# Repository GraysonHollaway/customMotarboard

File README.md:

# Custom Motarboard
Gerber and KiCad files used to make a custom mortarboard decoration for graduation.
This custom PCB sits on top of your gaduation cap and spells out 'ECE OSU' in amber LEDs using a custom designed state machine. 
The clock was implemented with a monostable 555 timer producing an approxamate square wave with tau on the order of 100 milliseconds 
The LEDs are contolled with an NPN BJT such that the digital and analog sections of the circuit are seperated.

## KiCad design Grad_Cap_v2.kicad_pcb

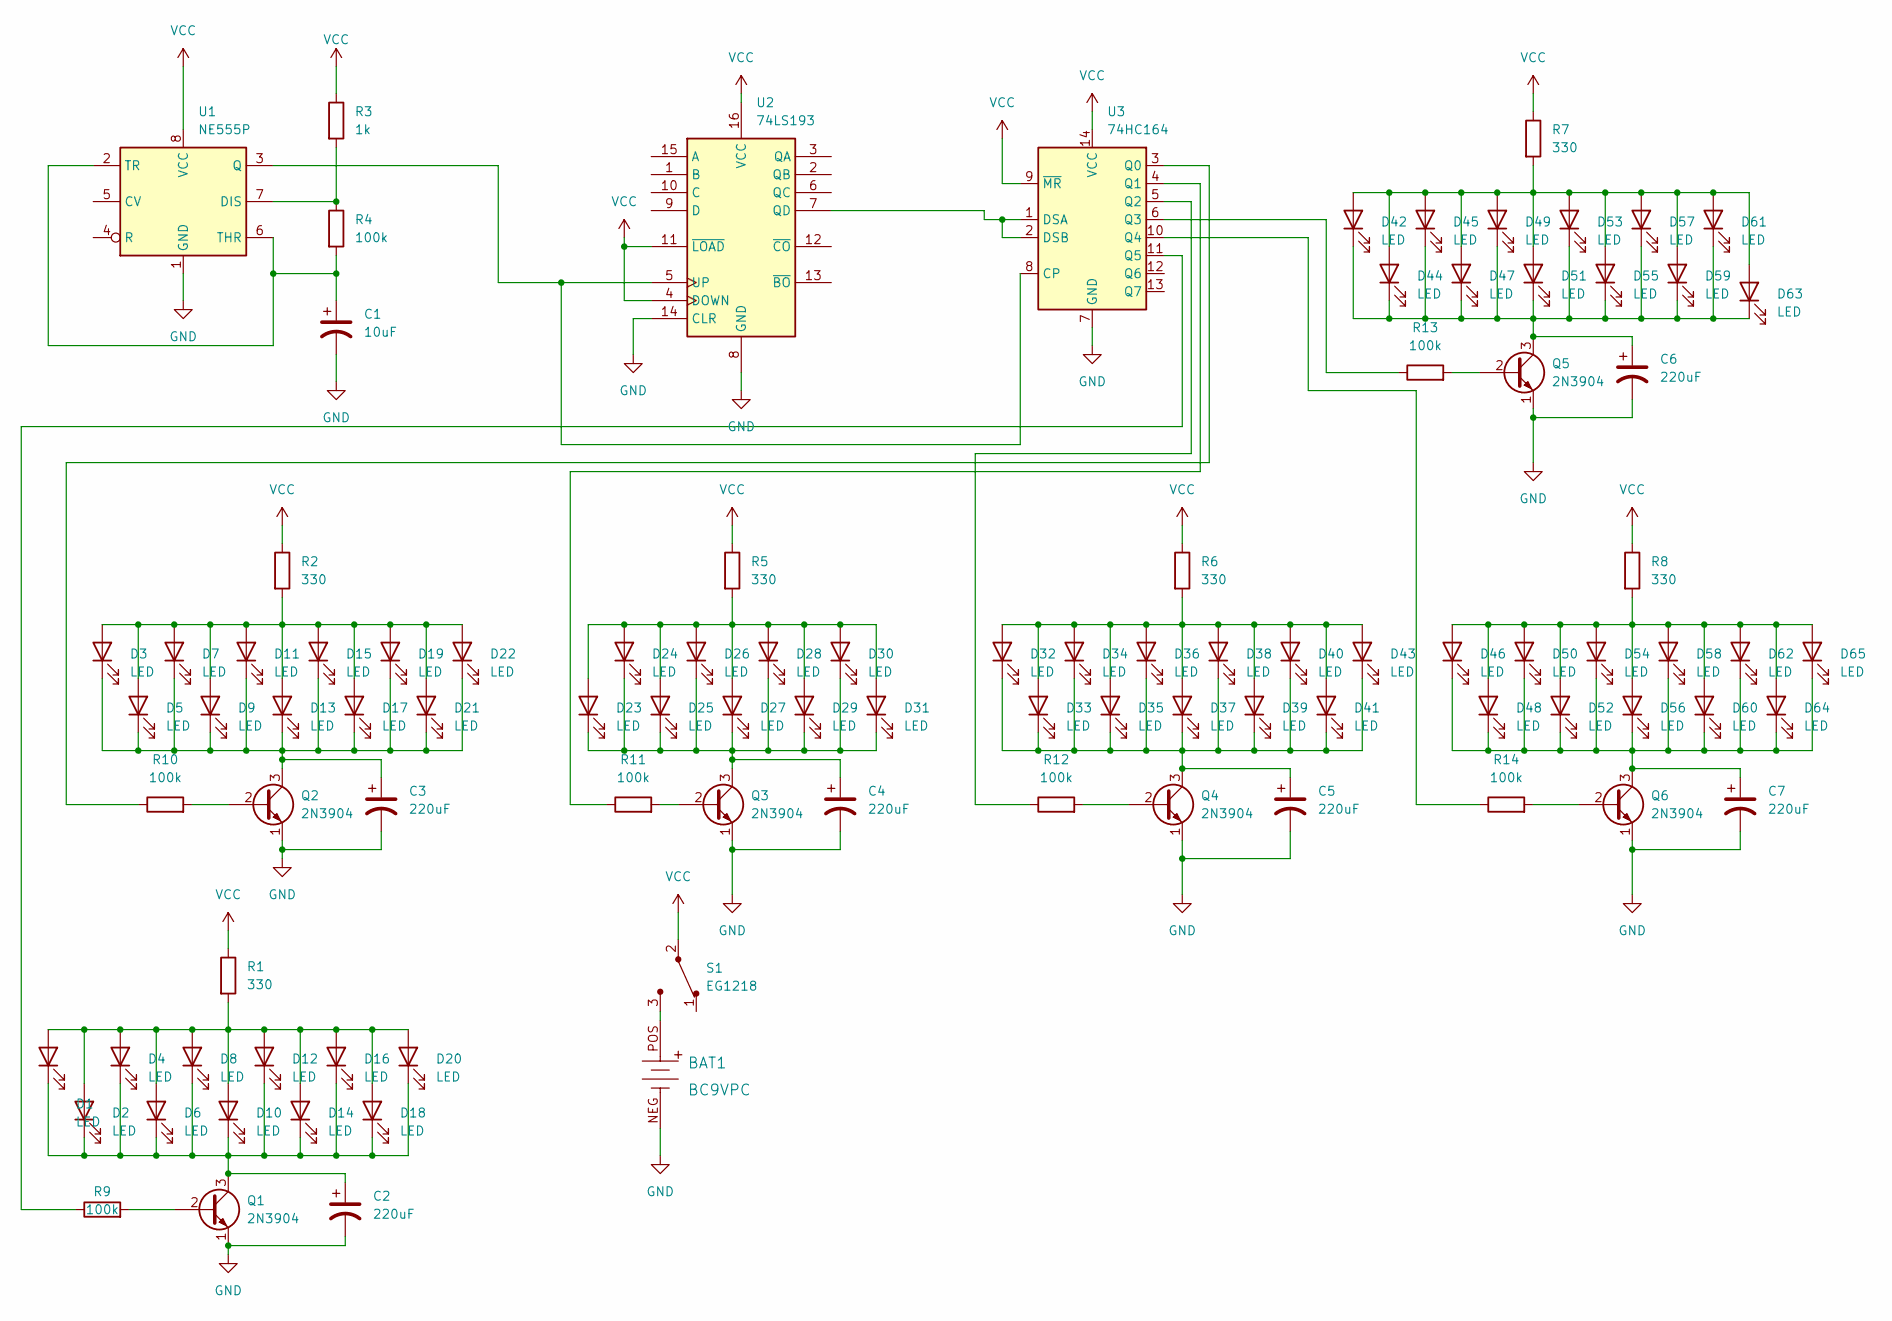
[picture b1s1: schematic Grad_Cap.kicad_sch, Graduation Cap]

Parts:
BAT1: BC9VPC; Battery_Holder_9V_BC9VPC-ND; MPN BC9VPC; Digi-Key_PN BC9VPC-ND
C1: 10uF; CP_Radial_D4.0mm_P2.00mm
C2, C3, C4, C5, C6, C7: 220uF; CP_Radial_D4.0mm_P2.00mm
D1, D2, D3, D4, D5, D6, D7, D8, D9, D10, D11, D12, D13, D14, D15, D16, D17, D18, D19, D20, D21, D22, D23, D24, D25, D26, D27, D28, D29, D30, D31, D32, D33, D34, D35, D36, D37, D38, D39, D40, D41, D42, D43, D44, D45, D46, D47, D48, D49, D50, D51, D52, D53, D54, D55, D56, D57, D58, D59, D60, D61, D62, D63, D64, D65: LED; LED_D5.0mm
Q1, Q2, Q3, Q4, Q5, Q6: 2N3904; TO-92_Inline
R1, R2, R5, R6, R7, R8: 330; R_Axial_DIN0309_L9.0mm_D3.2mm_P12.70mm_Horizontal
R3: 1k; R_Axial_DIN0309_L9.0mm_D3.2mm_P12.70mm_Horizontal
R4, R9, R10, R11, R12, R13, R14: 100k; R_Axial_DIN0309_L9.0mm_D3.2mm_P12.70mm_Horizontal
S1: EG1218; Switch_Slide_11.6x4mm_EG1218; MPN EG1218; Digi-Key_PN EG1903-ND
U1: NE555P; DIP-8_W7.62mm
U2: 74LS193; DIP-16_W7.62mm_Socket
U3: 74HC164; DIP-14_W7.62mm

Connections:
GND: BAT1.NEG, C1.2, C2.2, C3.2, C4.2, C5.2, C6.2, C7.2, Q1.1 (E), Q2.1 (E), Q3.1 (E), Q4.1 (E), Q5.1 (E), Q6.1 (E), U1.1 (GND), U2.8 (GND), U2.14 (CLR), U3.7 (GND)
unnamed: BAT1.POS, S1.3
unnamed: C1.1, R4.2, U1.2 (TR), U1.6 (THR)
unnamed: C2.1, D1.1 (K), D2.1 (K), D4.1 (K), D6.1 (K), D8.1 (K), D10.1 (K), D12.1 (K), D14.1 (K), D16.1 (K), D18.1 (K), D20.1 (K), Q1.3 (C)
unnamed: C3.1, D3.1 (K), D5.1 (K), D7.1 (K), D9.1 (K), D11.1 (K), D13.1 (K), D15.1 (K), D17.1 (K), D19.1 (K), D21.1 (K), D22.1 (K), Q2.3 (C)
unnamed: C4.1, D23.1 (K), D24.1 (K), D25.1 (K), D26.1 (K), D27.1 (K), D28.1 (K), D29.1 (K), D30.1 (K), D31.1 (K), Q3.3 (C)
unnamed: C5.1, D32.1 (K), D33.1 (K), D34.1 (K), D35.1 (K), D36.1 (K), D37.1 (K), D38.1 (K), D39.1 (K), D40.1 (K), D41.1 (K), D43.1 (K), Q4.3 (C)
unnamed: C6.1, D42.1 (K), D44.1 (K), D45.1 (K), D47.1 (K), D49.1 (K), D51.1 (K), D53.1 (K), D55.1 (K), D57.1 (K), D59.1 (K), D61.1 (K), D63.1 (K), Q5.3 (C)
unnamed: C7.1, D46.1 (K), D48.1 (K), D50.1 (K), D52.1 (K), D54.1 (K), D56.1 (K), D58.1 (K), D60.1 (K), D62.1 (K), D64.1 (K), D65.1 (K), Q6.3 (C)
unnamed: D1.2 (A), D2.2 (A), D4.2 (A), D6.2 (A), D8.2 (A), D10.2 (A), D12.2 (A), D14.2 (A), D16.2 (A), D18.2 (A), D20.2 (A), R1.2
unnamed: D3.2 (A), D5.2 (A), D7.2 (A), D9.2 (A), D11.2 (A), D13.2 (A), D15.2 (A), D17.2 (A), D19.2 (A), D21.2 (A), D22.2 (A), R2.2
unnamed: D23.2 (A), D24.2 (A), D25.2 (A), D26.2 (A), D27.2 (A), D28.2 (A), D29.2 (A), D30.2 (A), D31.2 (A), R5.2
unnamed: D32.2 (A), D33.2 (A), D34.2 (A), D35.2 (A), D36.2 (A), D37.2 (A), D38.2 (A), D39.2 (A), D40.2 (A), D41.2 (A), D43.2 (A), R6.2
unnamed: D42.2 (A), D44.2 (A), D45.2 (A), D47.2 (A), D49.2 (A), D51.2 (A), D53.2 (A), D55.2 (A), D57.2 (A), D59.2 (A), D61.2 (A), D63.2 (A), R7.2
unnamed: D46.2 (A), D48.2 (A), D50.2 (A), D52.2 (A), D54.2 (A), D56.2 (A), D58.2 (A), D60.2 (A), D62.2 (A), D64.2 (A), D65.2 (A), R8.2
unnamed: Q1.2 (B), R9.2
unnamed: Q2.2 (B), R10.2
unnamed: Q3.2 (B), R11.2
unnamed: Q4.2 (B), R12.2
unnamed: Q5.2 (B), R13.2
unnamed: Q6.2 (B), R14.2
unnamed: R3.2, R4.1, U1.7 (DIS)
unnamed: R9.1, U3.11 (Q5)
unnamed: R10.1, U3.3 (Q0)
unnamed: R11.1, U3.4 (Q1)
unnamed: R12.1, U3.5 (Q2)
unnamed: R13.1, U3.6 (Q3)
unnamed: R14.1, U3.10 (Q4)
unnamed: U1.3 (Q), U2.5 (UP), U3.8 (CP)
unnamed: U2.7 (QD), U3.1 (DSA), U3.2 (DSB)
VCC: R1.1, R2.1, R3.1, R5.1, R6.1, R7.1, R8.1, S1.2, U1.8 (VCC), U2.4 (DOWN), U2.11 (~LOAD), U2.16 (VCC), U3.9 (~MR), U3.14 (VCC)

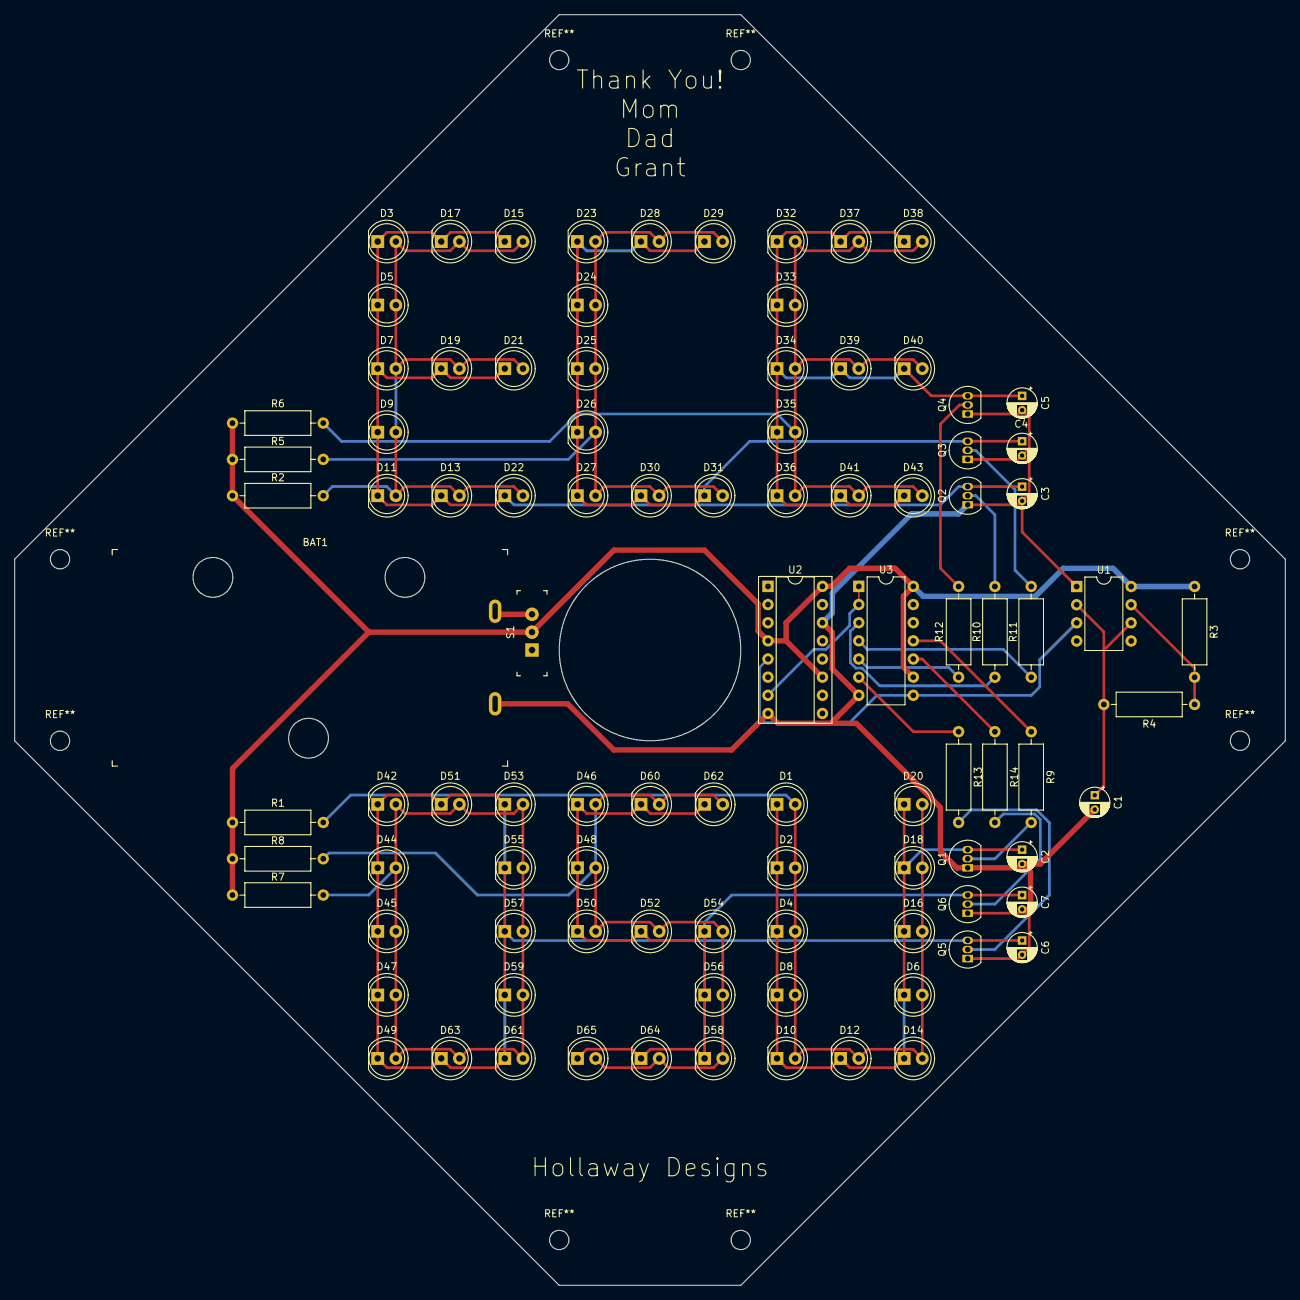
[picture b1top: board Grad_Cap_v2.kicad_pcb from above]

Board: 2 copper layers, 177.8 x 177.8 mm, 97 parts (0 on the bottom side), 31 nets.

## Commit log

2022-05-10 All Gerber files added
2022-05-10 Add files via upload
    KiCad files added
2022-05-10 Update README.md
    Update detail
